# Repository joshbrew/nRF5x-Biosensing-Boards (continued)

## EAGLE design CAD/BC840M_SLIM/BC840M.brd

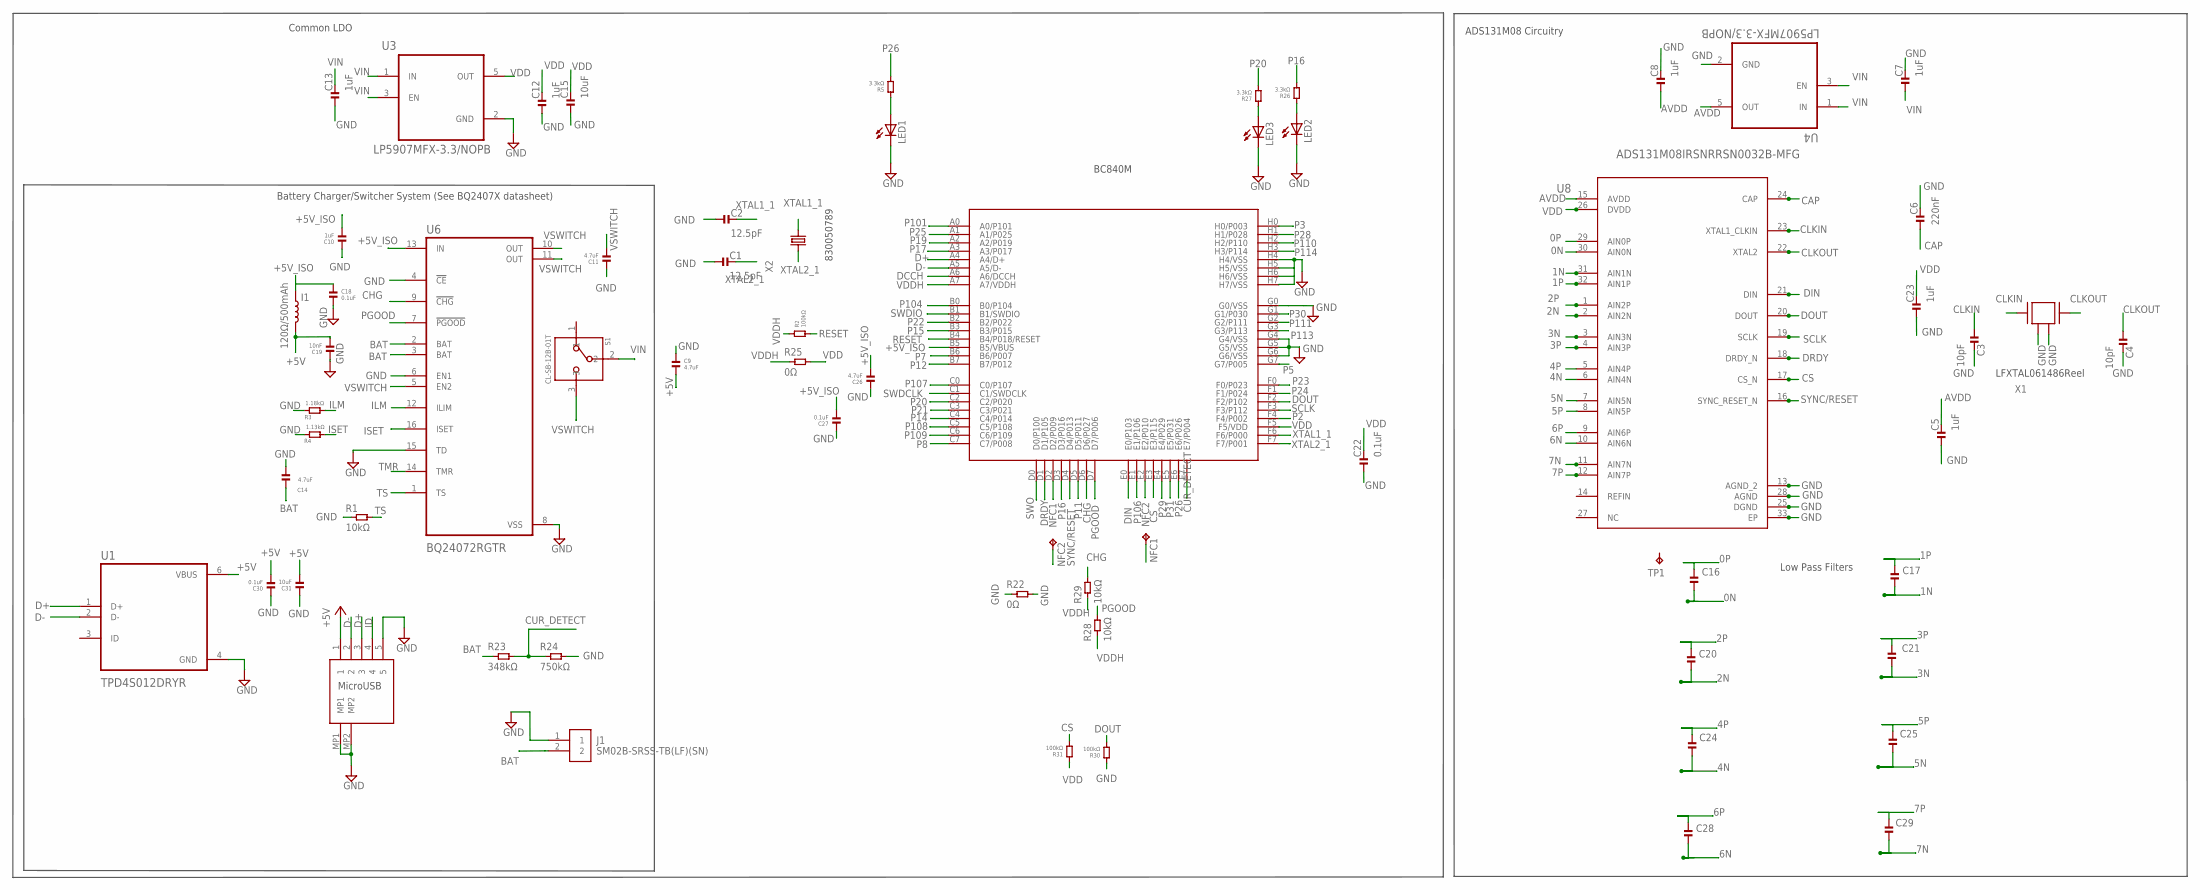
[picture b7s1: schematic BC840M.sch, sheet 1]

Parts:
C1, C2: 12.5pF; 0201
C3, C4: 10pF; 0201
C5, C7, C8, C10, C12, C13, C23: 1uF; 0201
C6: 220nF; 0201
C9, C11, C14, C26: 4.7uF; 0201
C15, C31: 10uF; 0402
C16, C17, C20, C21, C24, C25, C28, C29: 100pF; 0201
C18, C22, C27, C30: 0.1uF; 0201
C19: 10nF; 0201
I1: 120Ω/500mAh; 0402_COILCRAFT
J1: SM02B-SRSS-TB(LF)(SN)
LED1, LED2, LED3: LEDCHIPLED_0603; CHIPLED_0603
NFC1, NFC2: TPTP14SQ; TP14SQ
R1: 10kΩ; 0201
R2: 100kΩ; 0201
R3: 1.18kΩ; 0603
R4: 1.13kΩ; 0603
R5, R26, R27: 3.3kΩ; 0201
R22, R25: 0Ω; 0805
R23: 348kΩ; 0603
R24: 750kΩ; 0603
R28, R29: 10kΩ; 0402
R30, R31: 100kΩ; 0402
S1: CL-SB-12B-01T; CL-SB-12B
TP1: TPTP15R; TP15R
U1: TPD4S012DRYR; PSON50P145X100X60-6N
U2: BC840M
U3, U4: LP5907MFX-3.3/NOPB; SOT95P280X145-5N
U6: BQ24072RGTR; QFN50P300X300X100-17N
U7: DX4R005JJ2R1800
U8: ADS131M08IRSNRRSN0032B-MFG; RSN0032B-MFG
X1: ABM3B-8.000MHZ-B2-T
X2: FC-12M

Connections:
0N: C16.2, U8.30 (AIN0N)
0P: C16.1, U8.29 (AIN0P)
1N: C17.2, U8.31 (AIN1N)
1P: C17.1, U8.32 (AIN1P)
2N: C20.2, U8.2 (AIN2N)
2P: C20.1, U8.1 (AIN2P)
3N: C21.2, U8.3 (AIN3N)
3P: C21.1, U8.4 (AIN3P)
4N: C24.2, U8.6 (AIN4N)
4P: C24.1, U8.5 (AIN4P)
5N: C25.2
5P: C25.1
6N: C28.2, U8.10 (AIN6N)
6P: C28.1, U8.9 (AIN6P)
7N: C29.2, U8.11 (AIN7N)
7P: C29.1, U8.12 (AIN7P)
+5V: C9.2, C19.2, C30.2, C31.2, I1.P$2 (2), U1.6 (VBUS), U7.1
+5V_ISO: C10.2, C18.1, C26.2, C27.2, I1.P$1 (1), U2.B5 (B5/VBUS), U6.13 (IN)
AVDD: C5.2, C8.1, U4.5 (OUT), U8.15 (AVDD)
BAT: C14.2, J1.2, R23.1, U6.2 (BAT), U6.3 (BAT)
CAP: C6.1, U8.24 (CAP)
CHG: R29.2, U2.D6 (D6/P027), U6.9 (!CHG)
CLKIN: C3.1, U8.23 (XTAL1_CLKIN), X1.1
CLKOUT: C4.1, U8.22 (XTAL2), X1.3
CS: R31.1, U2.E3 (E3/P115), U8.17 (CS_N)
CUR_DETECT: R23.2, R24.1, U2.E7 (E7/P004)
D+: U1.1 (D+), U2.A4 (A4/D+), U7.3
D-: U1.2 (D-), U2.A5 (A5/D-), U7.2
DCCH: U2.A6 (A6/DCCH)
DIN: U2.E0 (E0/P103), U8.21 (DIN)
DOUT: R30.1, U2.F2 (F2/P102), U8.20 (DOUT)
DRDY: U2.D1 (D1/P105), U8.18 (DRDY_N)
GND: C1.1, C2.1, C3.2, C4.2, C5.1, C6.2, C7.2, C8.2, C9.1, C10.1, C11.1, C12.1, C13.1, C14.1, C15.1, C18.2, C19.1, C22.1, C23.1, C26.1, C27.1, C30.1, C31.1, J1.1, LED1.C, LED2.C, LED3.C, R1.1, R3.1, R4.1, R22.1, R22.2, R24.2, R30.2, U1.4 (GND), U2.G0 (G0/VSS), U2.G4 (G4/VSS), U2.G5 (G5/VSS), U2.G6 (G6/VSS), U2.H4 (H4/VSS), U2.H5 (H5/VSS), U2.H6 (H6/VSS), U2.H7 (H7/VSS), U3.2 (GND), U4.2 (GND), U6.4 (!CE), U6.6 (EN1), U6.8 (VSS), U6.15 (TD), U7.5, U7.MP1, U7.MP2, U8.13 (AGND_2), U8.25 (DGND), U8.28 (AGND), U8.33 (EP), X1.2, X1.4
ID: U7.4
ILM: R3.2, U6.12 (ILIM)
ISET: R4.2, U6.16 (ISET)
LED1: LED1.A, R5.2
LED2: LED2.A, R26.2
LED3: LED3.A, R27.2
NFC1: NFC2.TP, U2.D2 (D2/P009)
NFC2: NFC1.TP, U2.E2 (E2/P010)
P2: U2.F4 (F4/P002)
P3: U2.H0 (H0/P003)
P5: U2.G7 (G7/P005)
P7: U2.B6 (B6/P007)
P8: U2.C7 (C7/P008)
P11: U2.D5 (D5/P011)
P12: U2.B7 (B7/P012)
P14: U2.C4 (C4/P014)
P15: U2.B3 (B3/P015)
P16: R26.1, U2.D3 (D3/P016)
P17: U2.A3 (A3/P017)
P19: U2.A2 (A2/P019)
P20: R27.1, U2.C2 (C2/P020)
P21: U2.C3 (C3/P021)
P22: U2.B2 (B2/P022)
P23: U2.F0 (F0/P023)
P24: U2.F1 (F1/P024)
P25: U2.A1 (A1/P025)
P26: R5.1, U2.E6 (E6/P026)
P28: U2.H1 (H1/P028)
P29: U2.E4 (E4/P029)
P30: U2.G1 (G1/P030)
P31: U2.E5 (E5/P031)
P101: U2.A0 (A0/P101)
P104: U2.B0 (B0/P104)
P106: U2.E1 (E1/P106)
P107: U2.C0 (C0/P107)
P108: U2.C5 (C5/P108)
P109: U2.C6 (C6/P109)
P110: U2.H2 (H2/P110)
P111: U2.G2 (G2/P111)
P113: U2.G3 (G3/P113)
P114: U2.H3 (H3/P114)
PGOOD: R28.2, U2.D7 (D7/P006), U6.7 (!PGOOD)
RESET: R2.1, U2.B4 (B4/P018/RESET)
SCLK: U2.F3 (F3/P112), U8.19 (SCLK)
SWDCLK: U2.C1 (C1/SWDCLK)
SWDIO: U2.B1 (B1/SWDIO)
SWO: U2.D0 (D0/P100)
SYNC/RESET: U2.D4 (D4/P013), U8.16 (SYNC_RESET_N)
TMR: U6.14 (TMR)
TS: R1.2, U6.1 (TS)
VDD: C12.2, C15.2, C22.2, C23.2, R25.2, R31.2, U2.F5 (F5/VDD), U3.5 (OUT), U8.26 (DVDD)
VDDH: R2.2, R25.1, R28.1, R29.1, U2.A7 (A7/VDDH)
VIN: C7.1, C13.2, S1.2, U3.1 (IN), U3.3 (EN), U4.1 (IN), U4.3 (EN)
VSWITCH: C11.2, S1.3, U6.5 (EN2), U6.10 (OUT), U6.11 (OUT)
XTAL1_1: C2.2, U2.F6 (F6/P000), X2.2
XTAL2_1: C1.2, U2.F7 (F7/P001), X2.1

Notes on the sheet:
LFXTAL061486Reel
830050789
MicroUSB
Battery Charger/Switcher System (See BQ2407X datasheet)
ADS131M08 Circuitry
Common LDO
BC840M
Low Pass Filters

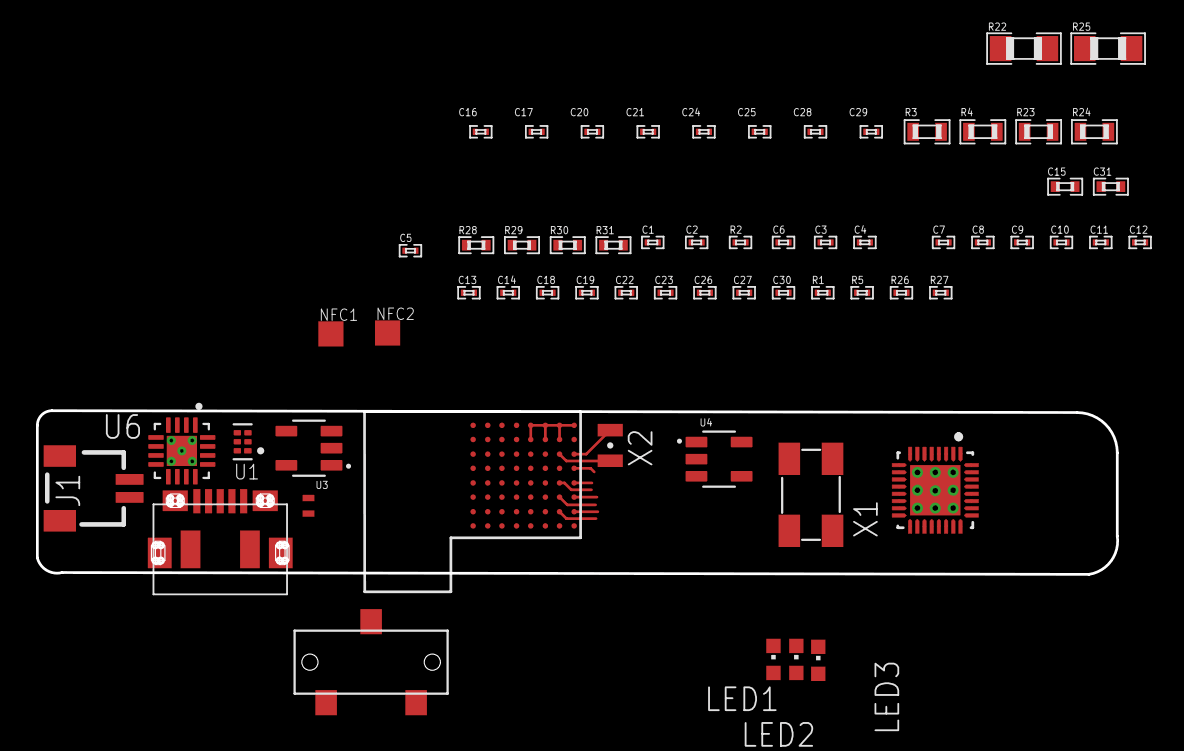
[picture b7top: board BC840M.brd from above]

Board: 2 copper layers, 60.0 x 9.1 mm, 64 parts (1 on the bottom side), 51 nets.

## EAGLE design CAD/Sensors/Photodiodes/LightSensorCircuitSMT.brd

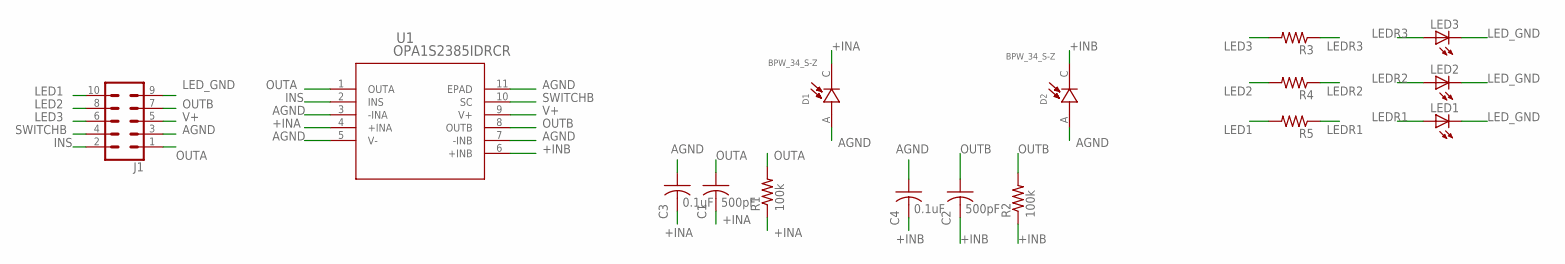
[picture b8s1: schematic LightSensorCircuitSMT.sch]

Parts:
C1, C2: 500pF; C0603
C3, C4: 0.1uF; C0603
D1, D2: BPW_34_S-Z; DIO_BPW_34_S-Z
J1: CONN_05X2NO_SILK; 2X5_NOSILK
LED1, LED2, LED3: LEDCHIPLED_1206; CHIPLED_1206
R1, R2: 100k; R0603
R3, R4, R5: R-US_R0603; R0603
U1: OPA1S2385IDRCR; DRC10_1P65X2P40_TEX

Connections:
+INA: C1.2, C3.2, D1.C, R1.1, U1.4 (+INA)
+INB: C2.2, C4.2, D2.C, R2.1, U1.6 (+INB)
AGND: C3.1, C4.1, D1.A, D2.A, J1.3, U1.3 (-INA), U1.5 (V-), U1.7 (-INB), U1.11 (EPAD)
INS: J1.2, U1.2 (INS)
LED1: J1.10, R5.2
LED2: J1.8, R4.2
LED3: J1.6, R3.2
LEDR1: LED1.A, R5.1
LEDR2: LED2.A, R4.1
LEDR3: LED3.A, R3.1
LED_GND: J1.9, LED1.C, LED2.C, LED3.C
OUTA: C1.1, J1.1, R1.2, U1.1 (OUTA)
OUTB: C2.1, J1.7, R2.2, U1.8 (OUTB)
SWITCHB: J1.4, U1.10 (SC)
V+: J1.5, U1.9 (V+)

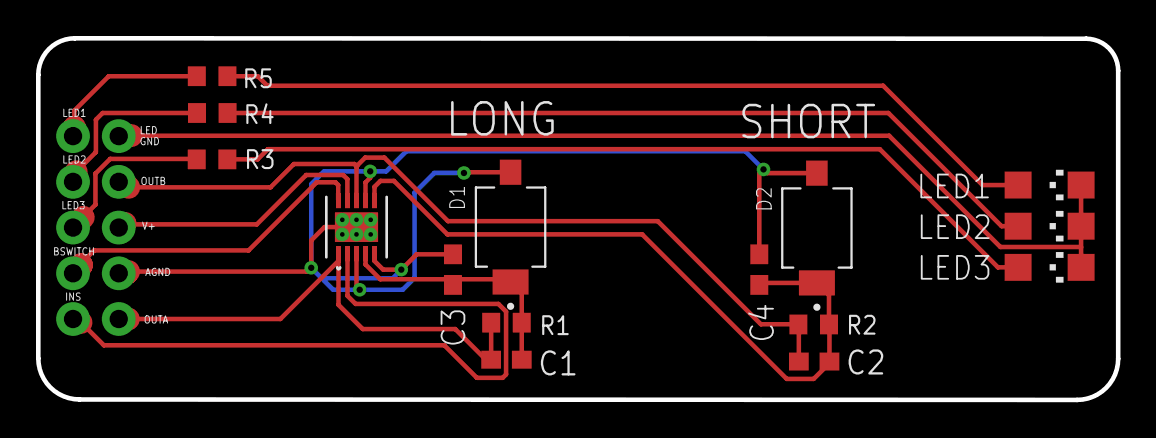
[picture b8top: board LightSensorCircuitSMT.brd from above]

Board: 2 copper layers, 60.0 x 20.1 mm, 16 parts (0 on the bottom side), 15 nets.

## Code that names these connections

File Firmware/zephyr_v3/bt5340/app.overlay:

// bt5340: complete carrier overlay; automatically loaded by Zephyr.
#include <zephyr/dt-bindings/gpio/gpio.h>
#include <zephyr/dt-bindings/pinctrl/nrf-pinctrl.h>
/ {
	aliases { bio-led = &led0; ads0 = &ads0; ads1 = &ads1; sensor-i2c = &i2c1; };
};
&led0 { gpios = <&gpio1 6 GPIO_ACTIVE_HIGH>; };
&led1 { gpios = <&gpio0 19 GPIO_ACTIVE_HIGH>; status = "disabled"; };
&led2 { gpios = <&gpio1 5 GPIO_ACTIVE_HIGH>; status = "disabled"; };
&led3 { status = "disabled"; };
&button0 { status = "disabled"; };
&button1 { status = "disabled"; };
&button2 { status = "disabled"; };
&button3 { status = "disabled"; };
&gpio_fwd { status = "disabled"; };
&uart0 { status = "disabled"; };
&uart1 { status = "disabled"; };
&spi4 { status = "disabled"; };
&qspi { status = "disabled"; };
&pwm0 { status = "disabled"; };
&nfct { status = "disabled"; };
&adc { status = "disabled"; };
&i2c0 { status = "disabled"; };
&spi1 { status = "disabled"; };
&spi0 {
	status = "okay";
	compatible = "nordic,nrf-spim";
	pinctrl-0 = <&bio_spi_default>;
	pinctrl-1 = <&bio_spi_sleep>;
	pinctrl-names = "default", "sleep";
	cs-gpios = <&gpio0 22 GPIO_ACTIVE_LOW>;
	ads0: adc@0 {
		compatible = "biosensing,ads131m08";
		reg = <0>;
		spi-max-frequency = <8000000>;
		drdy-gpios = <&gpio0 15 (GPIO_ACTIVE_LOW | GPIO_PULL_UP)>;
		reset-gpios = <&gpio0 12 GPIO_ACTIVE_LOW>;
	};
	// Uses cpuapp main.cpp extension mapping, NOT its conflicting overlay CS25.
	ads1: adc@1 {
		compatible = "biosensing,ads131m08";
		reg = <1>;
		spi-max-frequency = <8000000>;
		drdy-gpios = <&gpio0 11 (GPIO_ACTIVE_LOW | GPIO_PULL_UP)>;
		reset-gpios = <&gpio0 9 GPIO_ACTIVE_LOW>;
		status = "disabled";
	};
};
&i2c1 {
	status = "okay";
	clock-frequency = <400000>;
	pinctrl-0 = <&bio_i2c_default>;
	pinctrl-1 = <&bio_i2c_sleep>;
	pinctrl-names = "default", "sleep";
	bio_bme: bme280@76 { compatible = "bosch,bme280"; reg = <0x76>; };
};
&pinctrl {
	bio_spi_default: bio_spi_default { group1 { psels = <NRF_PSEL(SPIM_SCK, 0, 23)>, <NRF_PSEL(SPIM_MOSI, 0, 29)>, <NRF_PSEL(SPIM_MISO, 0, 20)>; }; };
	bio_spi_sleep: bio_spi_sleep { group1 { psels = <NRF_PSEL(SPIM_SCK, 0, 23)>, <NRF_PSEL(SPIM_MOSI, 0, 29)>, <NRF_PSEL(SPIM_MISO, 0, 20)>; low-power-enable; }; };
	bio_i2c_default: bio_i2c_default { group1 { psels = <NRF_PSEL(TWIM_SDA, 1, 2)>, <NRF_PSEL(TWIM_SCL, 1, 3)>; }; };
	bio_i2c_sleep: bio_i2c_sleep { group1 { psels = <NRF_PSEL(TWIM_SDA, 1, 2)>, <NRF_PSEL(TWIM_SCL, 1, 3)>; low-power-enable; }; };
};

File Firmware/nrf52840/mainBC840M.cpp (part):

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
#define DBG_LED             ((uint8_t)16)  //  16 (BC840M),    25 (BT840)     
#define MAX_INT             ((uint8_t)28)  //  28 (BC840M),     7 (BT840)
#define MPU_INT             ((uint8_t)2)   //  2 (BC840M),     38 (BT840)


#define PWM_CLK         ((uint32_t)8192000) //Frequency (Hz)
#define PWM_PERIOD_NSEC ((uint8_t)122) //1/Frequency in nanosec
#define PWM_PIN         ((uint8_t)37) //(BT840 draft 1 missing the CLKOUT pin in same position)


static const uint8_t samplesPerLED = 3;
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
/* MPU6050 Interrupt */
//TODO(bojankoce): Use Zephyr DT (device tree) macros to get GPIO device, port and pin number
    ret += configureGPIO(MPU_INT, GPIO_INPUT | GPIO_PULL_UP);
    ret += configureInterrupt(MPU_INT, GPIO_INT_EDGE_FALLING);
    ret += addGPIOCallback(MPU_INT, &mpu6050_callback,&mpu6050_irq_cb);

    if (ret != 0){
        LOG_ERR("***ERROR: GPIO initialization\n");
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}


// PWM // because we forgot the CLKOUT pin on a draft BT840/BT40 PCB

#include <drivers/pwm.h>

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        DATA_READY_GPIO, 
        ADS_RESET, 
        8192000
    ); // cs_pin, drdy_pin, sync_rst_pin, 8MHz SPI bus
    
    adc_1.init(
        ADS_1_CS, 
        DATA_READY_1_GPIO, 
        ADS_1_RESET, 
        8192000
    ); // cs_pin, drdy_pin, sync_rst_pin, 8MHz SPI bus

    max30102.Initialize();
    if(max30102.IsOnI2cBus()){
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    while(1){

#if 0        
    bool drdy = getGPIO(DATA_READY_GPIO);

    if(drdy) {
        adc.readAllChannels(adcRawData);
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
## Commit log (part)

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2021-05-31 upload new CAD files
2021-06-18 finished sch
2021-06-18 smaller packages
2021-06-18 edits
2021-06-18 add switch
2021-06-18 edityedits
2021-06-18 almost there
2021-06-18 moarrrr
2021-06-18 draft
2021-06-19 fixes
2021-06-20 more edits
2021-06-20 edeets
2021-06-20 edit
2021-06-24 replace with 20 pin cp2102
2021-06-25 pushed
2021-06-30 add both CP2102 versions
2021-11-13 moved
2021-11-14 i/o prerouting
2021-11-14 latest
2021-11-15 grounding routed
2021-11-16 removed cap on ads
2021-11-16 more tweaks
2021-11-18 touchups
2021-11-18 still need to add TVS diodes
2021-11-18 fixed a ground
2021-11-18 more layout fixes
2021-11-18 more fixes
2021-11-19 tweaks
2021-11-22 added TVS diodes
2021-11-23 push
2021-11-24 edits and CAM
2021-11-24 updated BOM
2021-11-24 fix holes for microusb
2021-11-28 fixed tented vias
2021-12-16 Create LICENSE
2022-05-28 added light sensor test circuits (plz dont buy all muh parts :3)
2022-06-07 add firmware test (it builds and flashes but still some runtime error)
2022-06-08 fix readme
2022-06-18 Adapt the code to BC840M that contains nRF52840 SoC
2022-06-28 Include MAX30102 module.
    Configure MAX30102 to work in preferred mode. Take the RED/IR samples from a FIFO, take the temperature reading and transfer the RED/IR samples together with the temperature over BLE using MAX30102 C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
2022-06-29 Add ControlCharacteristicWrite callback function to handle command/config messages received from the smartphone/PC
2022-06-30 Check if MAX30102 is attached on I2C bus before start sampling.
2022-07-05 Add MPU6050 module
2022-07-20 Add the second ADS131M08 sensor.
    Create separate BLE characteristics for sending samples of second ADS131M08 sensor.
2022-07-30 Add the ability to transfer sensor readings over USB serial link
2022-08-06 Include packet number Byte in MAX30102 data packet
2022-08-11 added tweaked max30102 settings
2022-08-15 Send data over USB only if initialized. Don't block BLE transfer and the rest of initialization.
2022-08-22 Take samples from BME280 sensor. Send samples over BLE and USB.
2022-08-28 add diagram
2022-08-29 Remove HEXDUMP debug print from Bme280Notify function
2022-08-30 design corrections
2022-08-30 added missing voltage divider (doesn't fix the battery charger circuit)
2022-09-06 Slightly change ADS131M08 initial configuration. Write 0 to RESET bit, enable DC Block Filter.
2022-09-07 Figure out if we have BMP280 or BME280 on I2C bus before sampling. Send the appropriate data over BLE/USB.
2022-09-23 merged latest
2022-10-02 added revisions and alt configurations
2022-10-02 updated image
2022-10-05 add cam outputs for bt series with some corrections
2022-12-03 nRF5340 port. cpuapp and cpunet folders
    create cpunet folder for Network core. create cpuapp folder for Application core.
2022-12-15 trying to edit pin config
2022-12-15 fxed pin defs
2022-12-16 firmware working
2023-01-02 Periodically report RSSI over separate BLE Characteristic
2023-01-21 Modify MAX30102 Power up sequence
    Read Interrupt status register first.
2023-01-22 reorganized repo to include each firmware revision
2023-03-16 fixed CLKOUT GPIO pin missing, replaced P105 breakout
2023-03-16 adjusted default connection interval for nrf53 board
2023-04-13 Revert "Update main.cpp"
    This reverts commit bce8450d0689d8455b72e821ff1afdeaa58f89e8.
2023-04-13 fixed LED routine
2023-04-15 fix logic, add ambient toggle
2023-04-23 fixed nr52840 firmware for BC840M
2023-04-26 rollbacks to fix build
2023-04-27 fixed overlay
2023-04-27 fixed blink routine
2023-05-03 add FNIRS carrier board, testing firmware
2023-05-10 Copy the content of CAD folder from main branch
2023-05-13 Add logic for QMC5883L sensor sampling and sending over BLE&USB
2023-05-31 Add new BLE characteristic for sending Commands
    Add appropriate infrastructure for triggering appropriate callbacks depending on the BLE command.
2023-05-31 Add BLE Command callback for receiving commands over BLE
    Currently, Start/Stop sampling commands are implemented.
2023-05-31 Add Ble command callback for BME280 sensor
    Create a single file for storing BLE commands.
2023-06-01 Add BLE command callback for MPU6050 sensor
2023-06-01 Add BLE command callback for MAX30102 sensor
2023-06-10 Add audio module that plays alarm
2023-06-10 Include audio module in main function.
2023-06-11 modifed io order on bt840, some nrf52840 firmware cleanup (need to update with compass and audio too)
2023-06-11 need to actually test this again
2023-06-11 fixed cur_detect compatibility for bt40/bt840
2023-06-11 broke out the last gpio
2023-06-12 fixed fnirs carrier board
2023-06-16 updated cam
2023-06-22 minor fix
2023-06-24 Add Digital Microphone (DMIC) module
2023-07-01 Add the possibility for FOTA update over BLE
2023-07-04 testing bt840
2023-07-08 clearer
2023-07-09 update to latest
2023-07-09 up to date
2023-07-17 replace
2023-07-26 tweaked i/o, updated pinout image
2023-07-27 tweak
2023-08-16 Start/Stop scanning from iBeacons
    Add new BLE Command for start/stop scanning for iBeacon devices.
2023-08-17 Filter iBeacon devices.
    When iBeacon is detected store the details into i_beacon data structure.
2023-08-17 Add iBeacon BLE Characteristic.
    Send data about iBeacon over iBeacon BLE Characteristic
2023-08-21 restored overlay/main gpio config, added Beacon support
2023-10-09 Add the driver for Tlc5940.
    Currently, only Init function is implemented
2023-10-09 enh(tlc): Update Init function
2023-10-09 enh(tlc): Update TLC Init function
    Add number of daisy-chained TLC chips as argument.
2023-10-10 enh(tlc): Implement Get/Set/SetAll functions
2023-10-16 Update nrf5340dk_nrf5340.overlay
    Change GPIOs that interface with TLC
2023-10-16 Update tlc5940 driver
    add Kconfig file to set the number of chained TLC devices, update tlc driver itself.
2023-10-16 Change default log level to INF in all modules
    Use DBG when the debug print is not important
2023-10-21 Add TLC initialization in main.
    Use LOG_DBG prints instead of LOG_INF. Set default LOG verbosity value to LOG_LEVEL_INF
2023-11-02 Add support for RP2040 communication over UART
    Enhance main.cpp file. Wrap every part of the main with
    #if CONFIG_USE_xxx
    #endif
    sequence that will allow to include/exclude particular sensors from building.
    Temporary disable USB_DEVICE_STACK in prj.conf. This was needed because it is in conflict with UART communication with RP2040.
2023-11-08 updated with uart3, tlc5940 support
2023-11-08 fixed uart3 pin
2023-11-08 readme
2023-11-09 added rp2040 test script to go with the uart
2023-11-11 LOG improvement
    Increase the size of RTT BUFFER. That way, we will not lose the debug logs.
    Remove CONFIG_LOG_BUFFER_SIZE because that one does not play any role when RTT backend is selected (RTT_BUFFER_SIZE counts).
2023-11-11 Improve LOG
    Increase the size of RTT BUFFER. That way, we will not lose the debug logs.
    Remove CONFIG_LOG_BUFFER_SIZE because that one does not play any role when RTT backend is selected (RTT_BUFFER_SIZE counts).
2023-11-11 Fix prj.conf
2023-11-11 Improve prj.conf
    - Remove CONFIG_USE_USB flag. It is added automatically as soon as some of the sensors that supports USB transfer is enabled (see "select USE_USB" flag in Kconfig file)
    - Fixe CONFIG_USE_BME280 flag
2023-11-11 Update Kconfig
    As soon as we select to use BME280 sensor, enable (set to =y) the following flags:
    - CONFIG_SENSOR
    - CONFIG_BME280
2023-11-11 Update main.cpp
    use CONFIG_USE_USB wrapper around usbCommHandler.
2023-11-11 fix, up max30102 power output
2023-12-18 updated pinout image
2024-01-10 pdfs for a couple boards
2024-01-11 fixed label on pinout image
2024-02-07 added rp2040 pwm sync script
2024-02-07 fix pin
2024-08-01 BLE fix
2024-08-01 udate rp240, add a standalone ads131 example
2024-08-01 comment out for now
2024-08-01 Revert "comment out for now"
    This reverts commit 8fdb90313b9b9d489def4012d5c264e219213388.
2024-08-01 Reapply "comment out for now"
    This reverts commit a7bad595d3a043978a6c04ab1608e9a60457a740.
2024-08-01 better fix, works fine on phone and desktop now
2024-08-02 spec ideas
2024-08-04 updated rp2040 script
2024-08-04 downclocked
2024-08-05 working uf2 instructions for windows (I hate cmake)
2024-08-05 fixed routine speed I think
2024-08-05 added some missing Transimpedance amp notes
2024-08-06 clarity
2024-08-06 added rgb indicator
2024-08-06 better hardware timer
2024-08-09 improving timing, not perfect yet
2024-08-10 better pwm program, not perfect yet
2024-11-29 added v3 cpuapp, has lots of build errors
